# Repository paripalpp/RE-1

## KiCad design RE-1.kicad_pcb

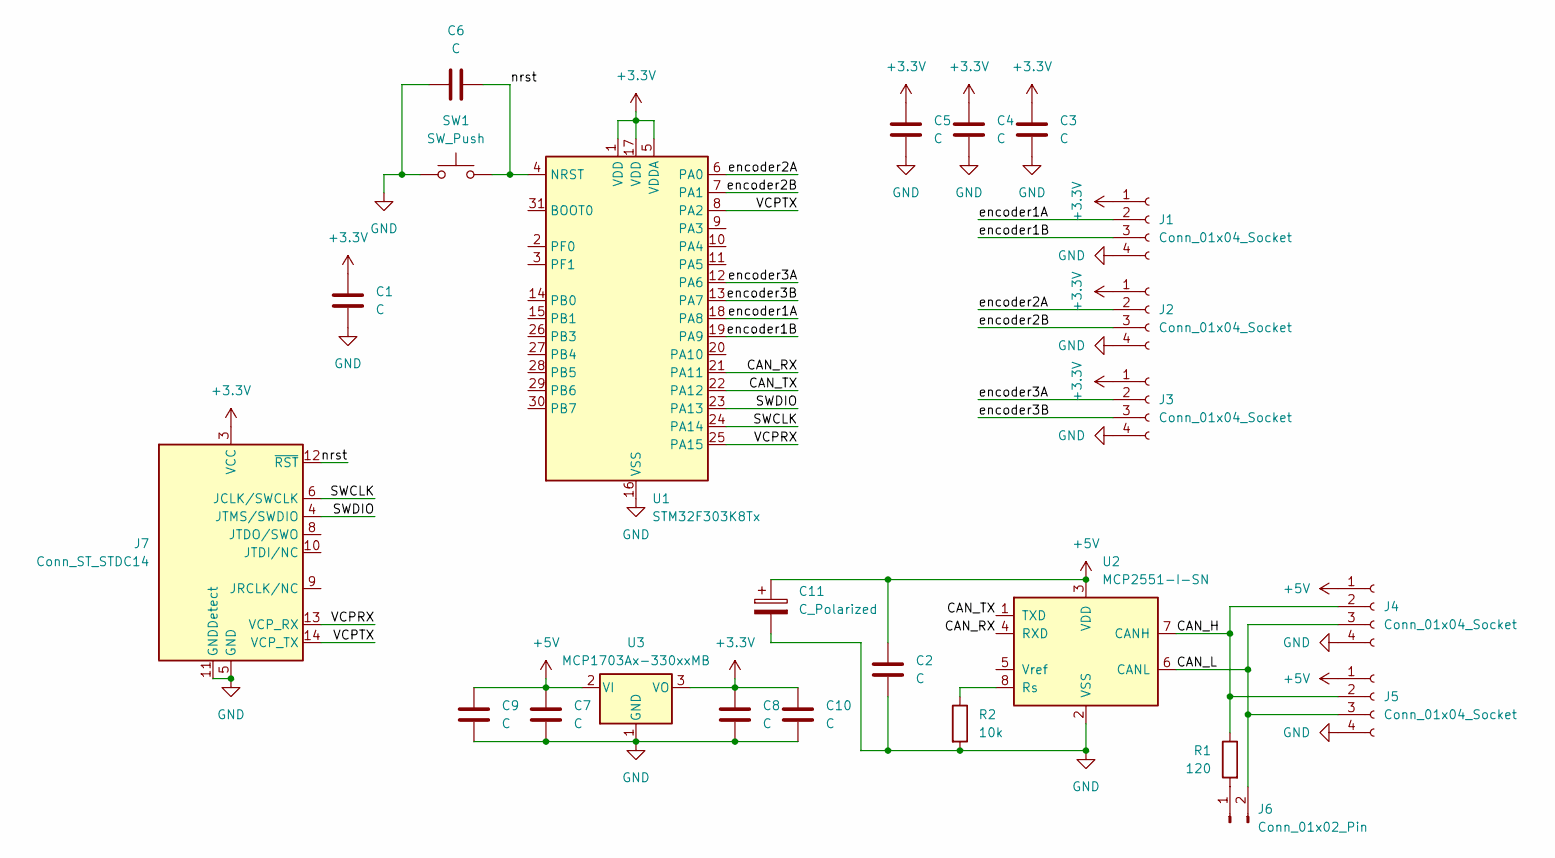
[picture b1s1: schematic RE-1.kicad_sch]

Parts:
C1, C2, C3, C4, C5, C6, C7, C8: C; C_0603_1608Metric
C9, C10: C; C_0805_2012Metric
C11: C_Polarized; CP_Elec_6.3x7.7
J1, J2, J3, J4, J5: Conn_01x04_Socket; JST_XA_S04B-XASK-1_1x04_P2.50mm_Horizontal
J6: Conn_01x02_Pin; PinHeader_1x02_P2.54mm_Vertical
J7: Conn_ST_STDC14; PinSocket_2x07_P1.27mm_Vertical_SMD
R1: 120; R_0603_1608Metric
R2: 10k; R_0603_1608Metric
SW1: SW_Push; TVAF06-A020B-R
U1: STM32F303K8Tx; LQFP-32_7x7mm_P0.8mm
U2: MCP2551-I-SN; SOIC-8_3.9x4.9mm_P1.27mm
U3: MCP1703Ax-330xxMB; SOT-89-3

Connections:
+3.3V: C1.1, C3.1, C4.1, C5.1, C8.1, C10.1, J1.1, J2.1, J3.1, J7.3 (VCC), U1.1 (VDD), U1.5 (VDDA), U1.17 (VDD), U3.3 (VO)
+5V: C2.1, C7.1, C9.1, C11.1, J4.1, J5.1, U2.3 (VDD), U3.2 (VI)
/CAN_H: J4.2, J5.2, R1.1, U2.7 (CANH)
/CAN_L: J4.3, J5.3, J6.2, U2.6 (CANL)
/CAN_RX: U1.21 (PA11), U2.4 (RXD)
/CAN_TX: U1.22 (PA12), U2.1 (TXD)
/SWCLK: J7.6 (JCLK/SWCLK), U1.24 (PA14)
/SWDIO: J7.4 (JTMS/SWDIO), U1.23 (PA13)
/VCPRX: J7.13 (VCP_RX), U1.25 (PA15)
/VCPTX: J7.14 (VCP_TX), U1.8 (PA2)
/encoder1A: J1.2, U1.18 (PA8)
/encoder1B: J1.3, U1.19 (PA9)
/encoder2A: J2.2, U1.6 (PA0)
/encoder2B: J2.3, U1.7 (PA1)
/encoder3A: J3.2, U1.12 (PA6)
/encoder3B: J3.3, U1.13 (PA7)
/nrst: C6.1, J7.12 (~RST), SW1.2, U1.4 (NRST)
GND: C1.2, C2.2, C3.2, C4.2, C5.2, C6.2, C7.2, C8.2, C9.2, C10.2, C11.2, J1.4, J2.4, J3.4, J4.4, J5.4, J7.5 (GND), J7.7 (GND), J7.11 (GNDDetect), R2.2, SW1.1, U1.16 (VSS), U1.32 (VSS), U2.2 (VSS), U3.1 (GND)
unnamed: J6.1, R1.2
unnamed: R2.1, U2.8 (Rs)

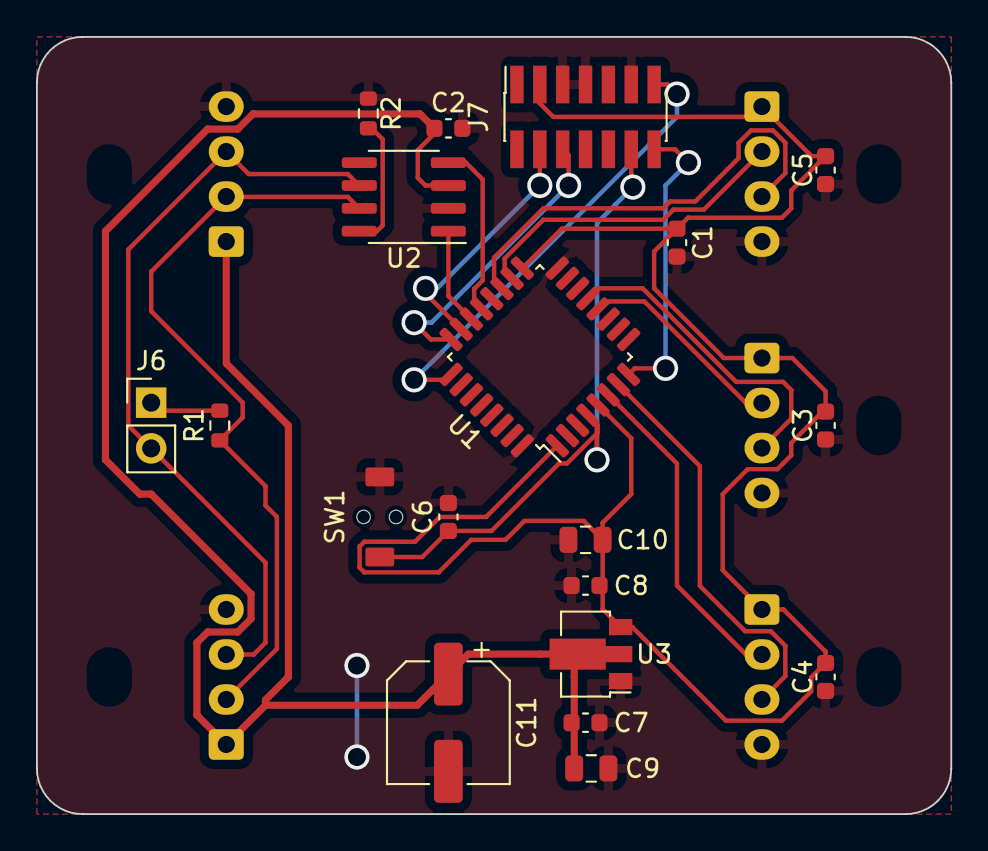
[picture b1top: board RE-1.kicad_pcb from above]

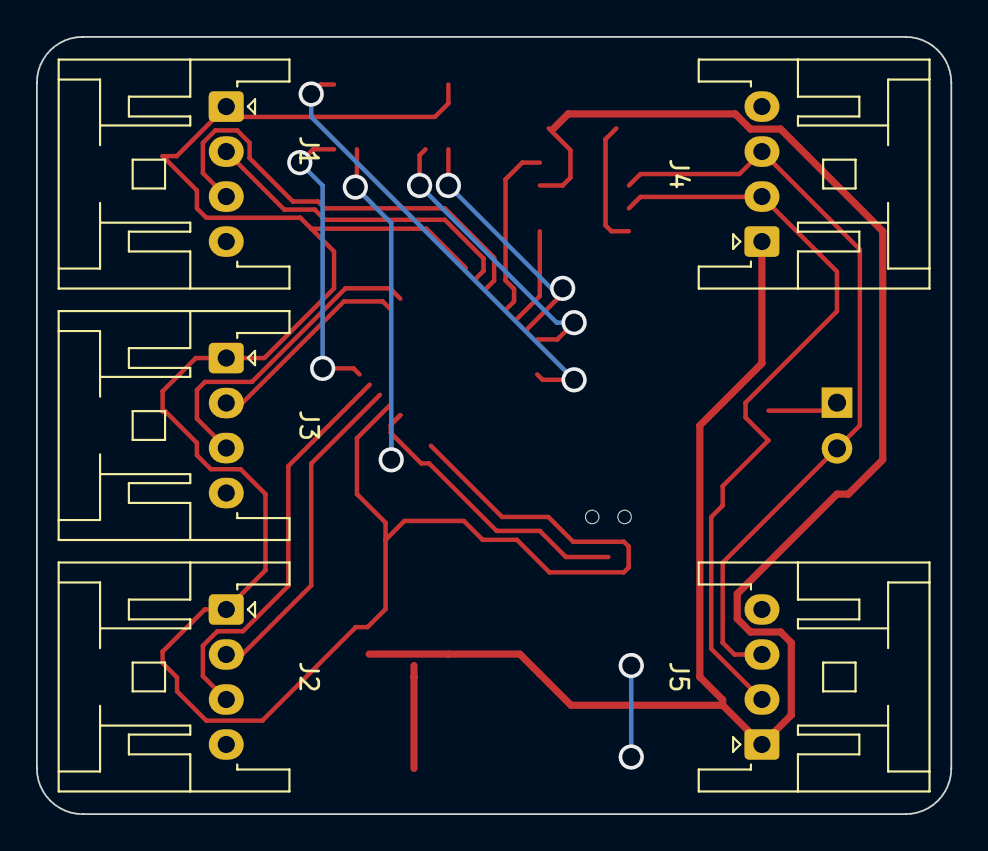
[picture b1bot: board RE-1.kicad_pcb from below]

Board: 2 copper layers, 50.8 x 43.2 mm, 24 parts (5 on the bottom side), 20 nets.

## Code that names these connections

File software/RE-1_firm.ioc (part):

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Mcu.Name=STM32F303C(6-8)Tx
Mcu.Package=LQFP48
Mcu.UserName=STM32F303C8Tx
PA0.Signal=S_TIM2_CH1_ETR
PA1.Signal=S_TIM2_CH2
PA11.Mode=CAN_Activate
PA11.Signal=CAN_RX
PA12.Mode=CAN_Activate
PA12.Signal=CAN_TX
PA6.Signal=S_TIM3_CH1
PA7.Signal=S_TIM3_CH2
PA8.Signal=S_TIM1_CH1
PA9.Signal=S_TIM1_CH2
PF0\ /\ OSC_IN.Mode=HSE-External-Oscillator
PF0\ /\ OSC_IN.Signal=RCC_OSC_IN
PF1\ /\ OSC_OUT.Mode=HSE-External-Oscillator
PF1\ /\ OSC_OUT.Signal=RCC_OSC_OUT
RCC.HSEPLLFreq_Value=8000000
RCC.HSE_VALUE=16000000
RCC.SYSCLKFreq_VALUE=72000000
RCC.SYSCLKSourceVirtual=RCC_SYSCLKSOURCE_PLLCLK
board=custom

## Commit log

2023-11-20 attached software
